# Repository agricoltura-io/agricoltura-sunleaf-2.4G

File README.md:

# agricoltura-sunleaf-2.4G
A new generation of the Sunleaf platform based on a STM32 2.4G radio module

Quick specs:
- ST Microelectronics STM32WB5MMGH6TR RF Module 
- BQ240210 Lithium Ion Solar/USB charge controller and battery management 
- 500mA Lithium Polymer battery with thermistor 
- I2C ports
- UART ports
- Analog ports
- Thread, Zigbee, Bluetooth 5.0

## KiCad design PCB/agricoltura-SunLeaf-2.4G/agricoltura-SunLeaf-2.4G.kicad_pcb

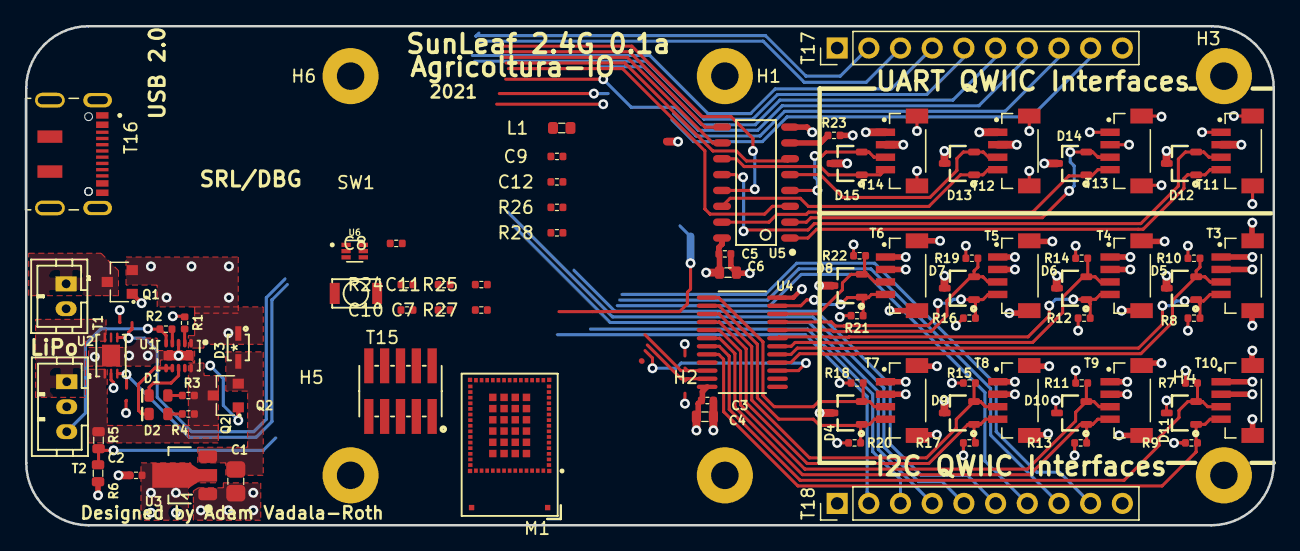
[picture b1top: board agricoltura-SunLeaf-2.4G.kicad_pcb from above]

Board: 4 copper layers, 100.0 x 40.0 mm, 90 parts (0 on the bottom side), 57 nets.

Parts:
C1: C0805C104M5RACTU; C0805
C2, C3, C5, C7, C8, C9, C10, C11, C12: C0402C104K9PACTU; R0402
C4, C6: GRM188R61A106KE69J; C0603
D1: LTST-C194TBKT; LED0603
D2: LTST-C194KGKT; LED0603
D3: BAT20JFILM
D4, D5, D6, D7, D8, D9, D10, D11, D12, D13, D14, D15: PESD3V3L2BT,215; SOT-23
H1, H2, H3, H4, H5, H6: M2_Plated_Hole; M2_HOLE
L1: MI0603K300R-10
M1: STM32WB5MMGH6TR
Q1, Q2: DMP3125L-7; SOT-23
R1: RC0402FR-07487RL; R0402
R2, R23: RC0402FR-071KL; R0402
R3, R4: RC0402FR-072KL; R0402
R5, R6: ERA-3AEB3741V; R0603
R7, R8, R9, R10, R11, R12, R13, R14, R15, R16, R17, R18, R19, R20, R21, R22: RC0402FR-074K7L; R0402
R24, R25, R26, R27, R28: RC0402FR-0710KL; R0402
SW1: B3U-1000P
T1: B2B-PH-K-S(LF)(SN)
T2: B3B-PH-K-S(LF)(SN)
T3, T4, T5, T6, T7, T8, T9, T10, T11, T12, T13, T14: BM04B-SRSS-TB(LF)(SN); CONN_BM04B-SRSS-TB(LF)(SN)
T15: 20021121-00010C4LF
T16: DX07S016JA1R1500; JAE_DX07S016JA1R1500
T17, T18: PPTC101LFBN-RC; Female_Header_Straight_1x10_Pitch2.54mm
U1: BQ24210DQCT; BQ24210
U2: LTC2941CDCB-1#TRMPBF; LTC2941CDCB-1-TRMPBF
U3: AZ1117CR-3.3TRG1; SOT_89
U4: TCA9548APWR
U5: 74HC4052D
U6: USBLC6-2P6; SOT50P160X60-6N

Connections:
+3V3: C2.1, C3.1, C4.1, C5.1, C6.1, C8.1, C9.1, C10.1, C11.1, C12.1, D4.3, D5.3, D6.3, D7.3, D8.3, D9.3, D10.3, D11.3, D12.3, D13.3, D14.3, D15.3, M1.4, M1.6, M1.15, M1.17, M1.32, R7.1, R8.1, R9.1, R10.1, R11.1, R12.1, R13.1, R14.1, R15.1, R16.1, R17.1, R18.1, R19.1, R20.1, R21.1, R22.1, R23.1, R24.1, R25.1, R27.1, R28.1, T3.2, T4.2, T5.2, T6.2, T7.2, T8.2, T9.2, T10.2, T11.2, T12.2, T13.2, T14.2, T15.1, U3.2, U4.24, U5.16
/I2C Mux & Connections/I2C_MUX1_RESET: M1.18, U4.3
/I2C Mux & Connections/I2C_SENSE1_SCL: M1.14, U4.22
/I2C Mux & Connections/I2C_SENSE1_SDA: M1.11, U4.23
/I2C Mux & Connections/QWIIC_SC0: D5.1, R8.2, T3.4, U4.5
/I2C Mux & Connections/QWIIC_SC1: D6.1, R12.2, T4.4, U4.7
/I2C Mux & Connections/QWIIC_SC2: D7.1, R16.2, T5.4, U4.9
/I2C Mux & Connections/QWIIC_SC3: D8.1, R21.2, T6.4, U4.11
/I2C Mux & Connections/QWIIC_SC4: D4.1, R20.2, T7.4, U4.14
/I2C Mux & Connections/QWIIC_SC5: D9.1, R17.2, T8.4, U4.16
/I2C Mux & Connections/QWIIC_SC6: D10.1, R13.2, T9.4, U4.18
/I2C Mux & Connections/QWIIC_SC7: D11.1, R9.2, T10.4, U4.20
/I2C Mux & Connections/QWIIC_SD0: D5.2, R10.2, T3.3, U4.4
/I2C Mux & Connections/QWIIC_SD1: D6.2, R14.2, T4.3, U4.6
/I2C Mux & Connections/QWIIC_SD2: D7.2, R19.2, T5.3, U4.8
/I2C Mux & Connections/QWIIC_SD3: D8.2, R22.2, T6.3, U4.10
/I2C Mux & Connections/QWIIC_SD4: D4.2, R18.2, T7.3, U4.13
/I2C Mux & Connections/QWIIC_SD5: D9.2, R15.2, T8.3, U4.15
/I2C Mux & Connections/QWIIC_SD6: D10.2, R11.2, T9.3, U4.17
/I2C Mux & Connections/QWIIC_SD7: D11.2, R7.2, T10.3, U4.19
/Power Supply & Battery Charging/3V3_REG_IN: C1.2, D3.2, Q2.2, U3.3
/Power Supply & Battery Charging/BAT: Q2.3, R3.2, R4.2, R5.1, U1.10, U2.1
/Power Supply & Battery Charging/BAT_SCL: M1.12, U2.3
/Power Supply & Battery Charging/BAT_SDA: M1.9, U2.4
/Power Supply & Battery Charging/BAT_VOLT_SENSE: R5.2, R6.1
/Power Supply & Battery Charging/CHG: D1.2, U1.8
/Power Supply & Battery Charging/PG6_EN7: D2.2, U1.6, U1.7
/Power Supply & Battery Charging/Solar_PNL: Q1.3, T1.1
/Power Supply & Battery Charging/THERM: R2.1, T2.3, U1.5
/Power Supply & Battery Charging/VTSB: R2.2, U1.4
/STM32 RF Module/BOOT0: M1.13, R28.2
/STM32 RF Module/JTAG_JTDI: M1.27, R25.2, T15.8
/STM32 RF Module/JTAG_JTDO: M1.48, T15.6
/STM32 RF Module/JTAG_NJTRST: M1.21, R27.2, T15.10
/STM32 RF Module/JTAG_SWCLK: M1.26, R26.1, T15.4
/STM32 RF Module/JTAG_SWDIO: M1.25, R24.2, T15.2
/STM32 RF Module/NRST: C7.1, M1.10, SW1.2
/STM32 RF Module/USB_D+: M1.29, U6.6
/STM32 RF Module/USB_D-: M1.30, U6.4
/UART Mux & Connections/UARTS1_RX: D12.1, T11.4, U5.1
/UART Mux & Connections/UARTS1_TX: D12.2, T11.3, U5.12
/UART Mux & Connections/UARTS2_RX: D13.1, T12.4, U5.14
/UART Mux & Connections/UARTS2_TX: D13.2, T12.3, U5.5
/UART Mux & Connections/UARTS3_RX: D14.1, T13.4, U5.15
/UART Mux & Connections/UARTS3_TX: D14.2, T13.3, U5.2
/UART Mux & Connections/UARTS4_RX: D15.1, T14.4, U5.11
/UART Mux & Connections/UARTS4_TX: D15.2, T14.3, U5.4
GND: C1.1, C2.2, C3.2, C4.2, C5.2, C6.2, C7.2, C8.2, C9.2, C10.2, C11.2, C12.2, L1.1, M1.5, M1.16, M1.31, M1.57, M1.58, M1.59, M1.60, M1.84, M1.86, R1.2, R6.2, R26.2, SW1.1, T1.2, T2.2, T3.1, T3.S1, T4.1, T4.S1, T5.1, T5.S1, T6.1, T6.S1, T7.1, T7.S1, T8.1, T8.S1, T9.1, T9.S1, T10.1, T10.S1, T11.1, T11.S1, T12.1, T12.S1, T13.1, T13.S1, T14.1, T14.S1, T15.3, T15.5, T15.9, T16.3, T16.9, U1.3, U1.11, U2.2, U2.7, U3.1, U4.12, U5.8, U6.2
unnamed: D1.1, R3.1
unnamed: D2.1, R4.1
unnamed: L1.2, T16.1, T16.12, T16.S1, T16.S2, T16.S3, T16.S4, T16.S5, T16.S6
unnamed: R1.1, U1.2
unnamed: R23.2, U5.7
unnamed: T2.1, U2.6
unnamed: T16.5, T16.8, U6.3
unnamed: T16.6, T16.7, U6.1
VBUS: D3.1, Q1.1, Q1.2, Q2.1, T16.2, T16.11, U1.1, U6.5

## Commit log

2021-04-07 Schematic and Board
    Imported project from other SunLeaf variant, inserted schematic for same radio as used on DarkLeaf/Finch-Feather. Board cleaned up and ready for routing in new hardware changes.
2024-03-26 Create License.md
    Added license
2024-03-26 KiCAD 8
    Projected updated to KiCAD 8

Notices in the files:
parts and their libraries:
Copyright 2016 Accelerated Designs. All rights reserved.
